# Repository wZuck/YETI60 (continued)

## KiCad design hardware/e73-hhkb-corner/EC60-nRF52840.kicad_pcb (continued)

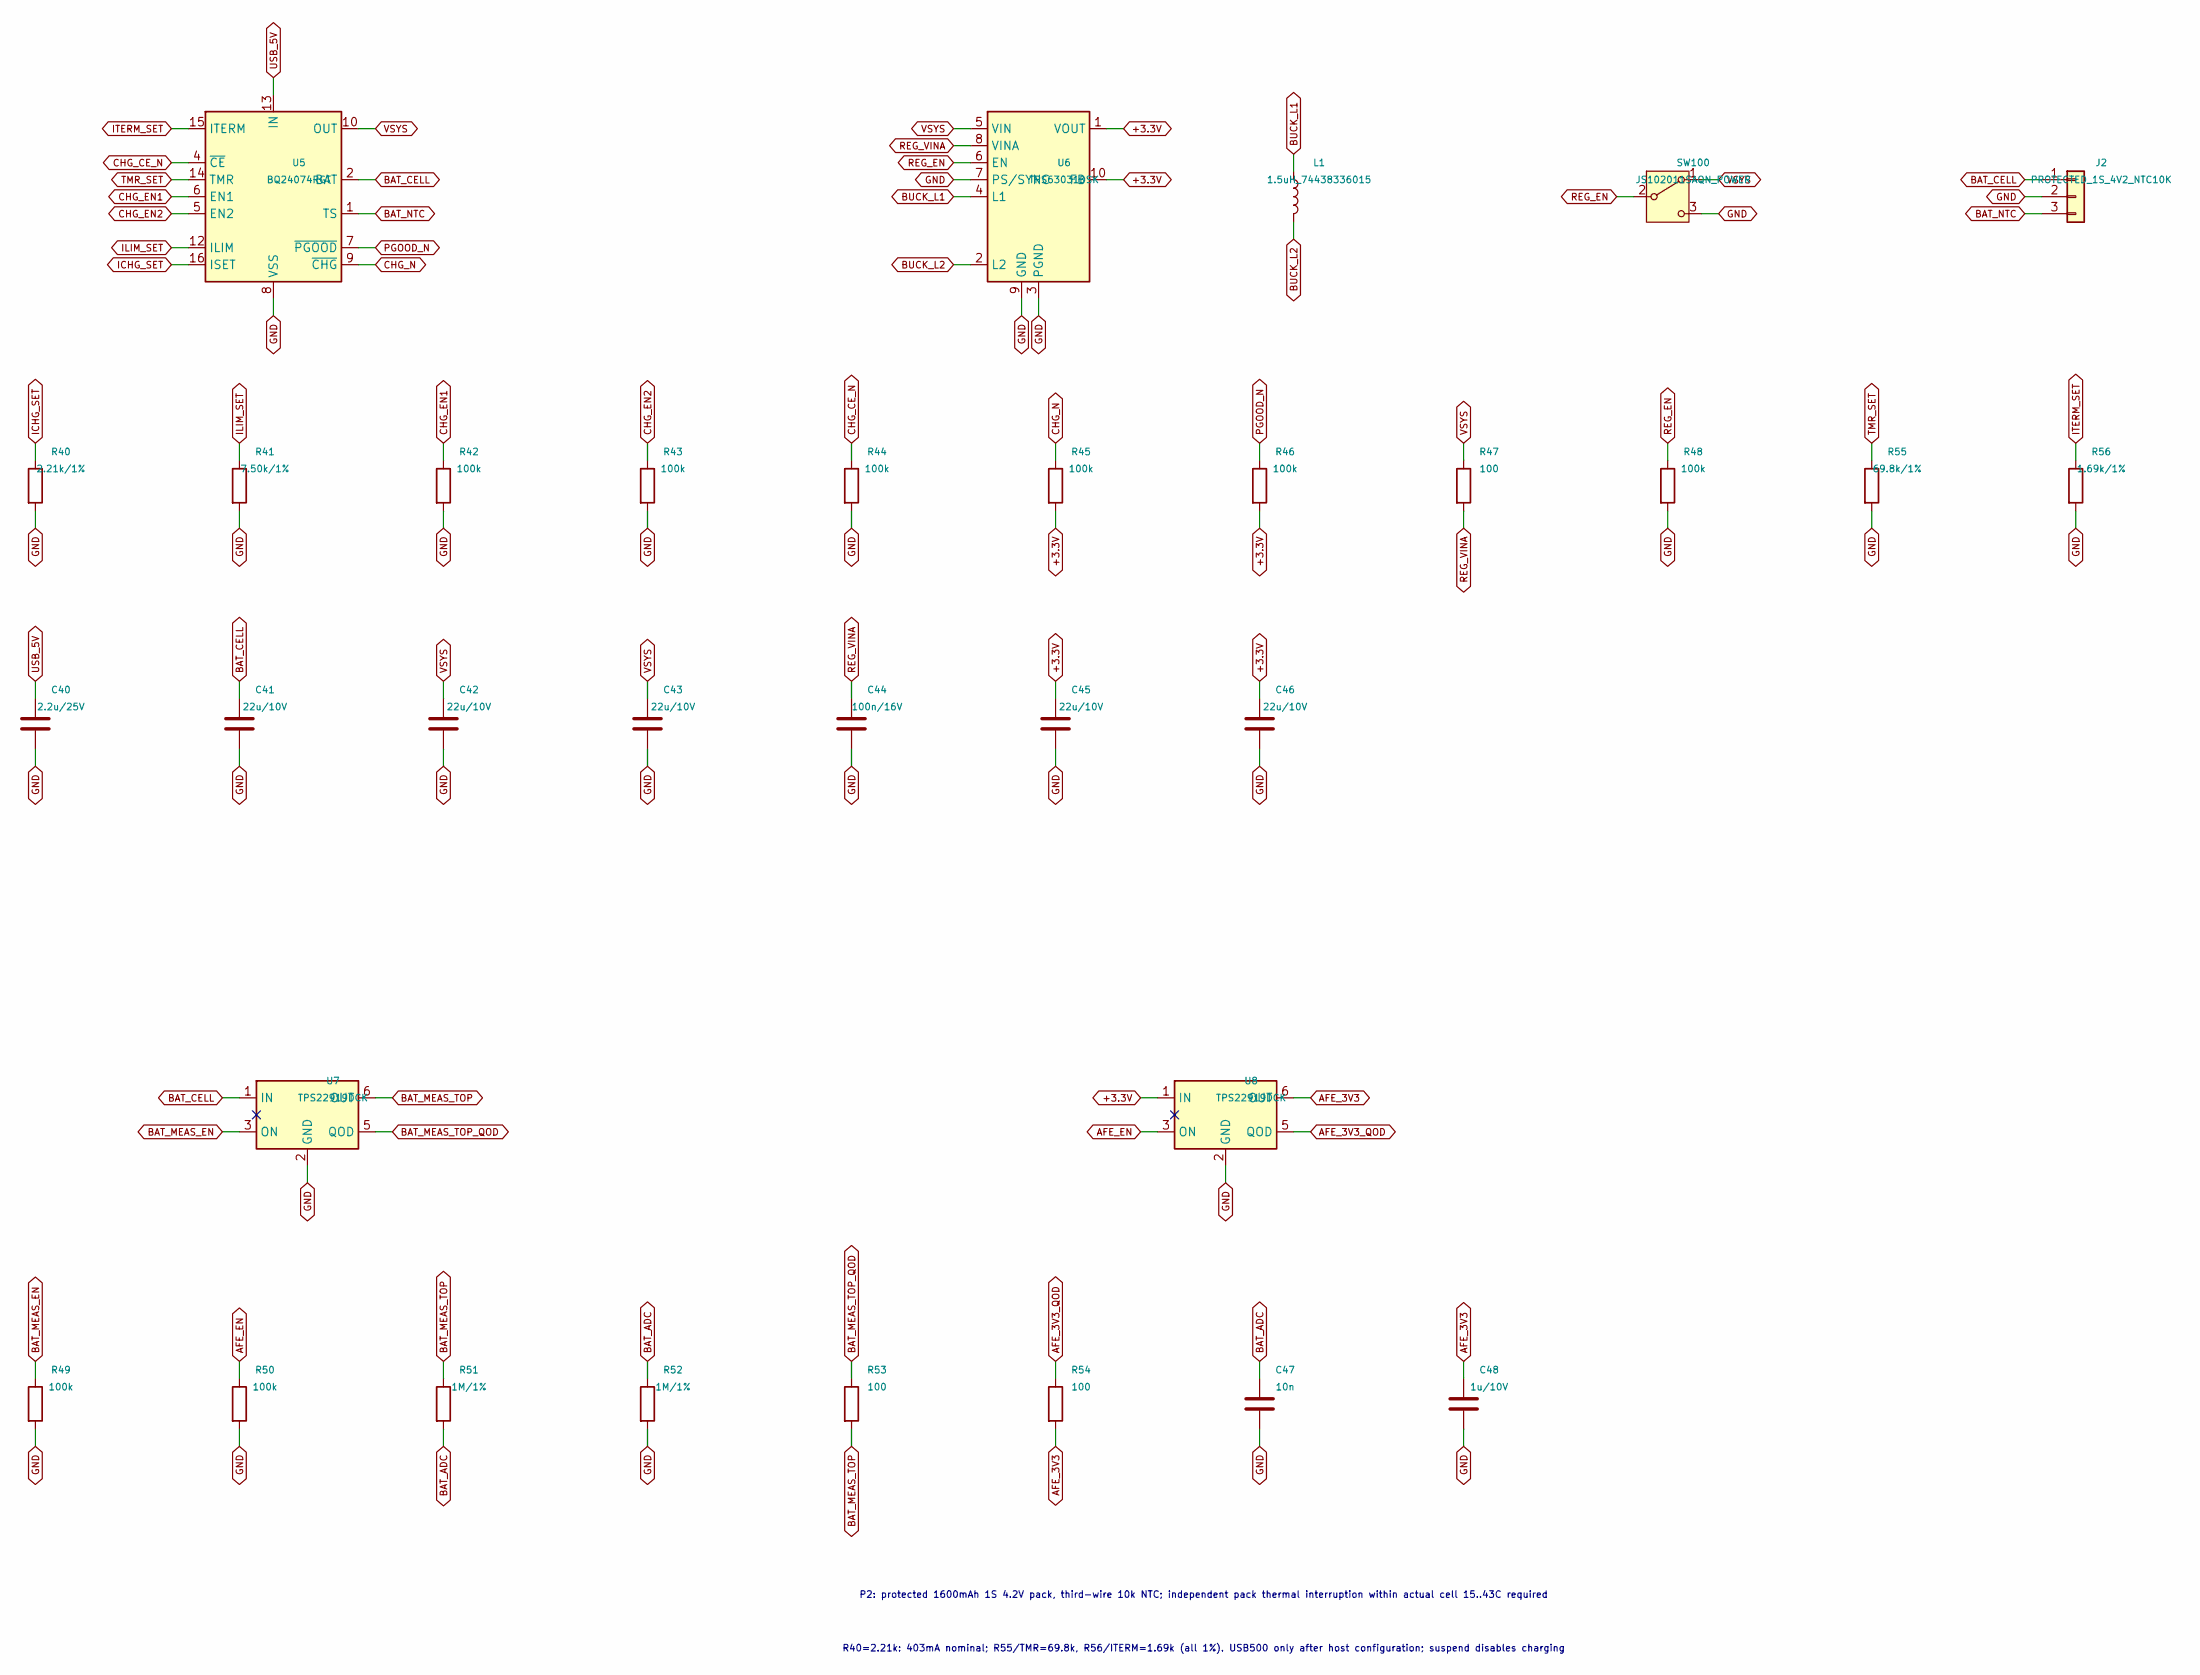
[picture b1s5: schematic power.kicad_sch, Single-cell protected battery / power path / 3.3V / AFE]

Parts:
C40: 2.2u/25V; C_0805_2012Metric__C40
C41: 22u/10V; C_0805_2012Metric__C41
C42: 22u/10V; C_0805_2012Metric__C42
C43: 22u/10V; C_0805_2012Metric__C43
C44: 100n/16V; C_0603_1608Metric__C44
C45: 22u/10V; C_0805_2012Metric__C45
C46: 22u/10V; C_0805_2012Metric__C46
C47: 10n; C_0402_1005Metric__C47
C48: 1u/10V; C_0402_1005Metric__C48
J2: PROTECTED_1S_4V2_NTC10K; JST_SH_SM03B-SRSS-TB_1x03-1MP_P1.00mm_Horizontal__J2
L1: 1.5uH_74438336015; L_Wuerth_MAPI-3015__L1
R40: 2.21k/1%; R_0402_1005Metric__R40
R41: 7.50k/1%; R_0402_1005Metric__R41
R42: 100k; R_0402_1005Metric__R42
R43: 100k; R_0402_1005Metric__R43
R44: 100k; R_0402_1005Metric__R44
R45: 100k; R_0402_1005Metric__R45
R46: 100k; R_0402_1005Metric__R46
R47: 100; R_0402_1005Metric__R47
R48: 100k; R_0402_1005Metric__R48
R49: 100k; R_0402_1005Metric__R49
R50: 100k; R_0402_1005Metric__R50
R51: 1M/1%; R_0402_1005Metric__R51
R52: 1M/1%; R_0402_1005Metric__R52
R53: 100; R_0402_1005Metric__R53
R54: 100; R_0402_1005Metric__R54
R55: 69.8k/1%; R_0402_1005Metric__R55
R56: 1.69k/1%; R_0402_1005Metric__R56
SW100: JS102011SAQN_POWER; SW_SPDT_CK_JS102011SAQN__SW100
U5: BQ24074RGT; VQFN-16-1EP_3x3mm_P0.5mm_EP1.6x1.6mm__U5
U6: TPS63031DSK; WSON-10-1EP_2.5x2.5mm_P0.5mm_EP1.2x2mm__U6
U7: TPS22919DCK; SOT-363_SC-70-6__U7
U8: TPS22919DCK; SOT-363_SC-70-6__U8

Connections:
+3.3V: C45.1, C46.1, R45.2, R46.2, U6.1 (VOUT), U6.10 (FB), U8.1 (IN); also elsewhere on the board
AFE_3V3_QOD: R54.1, U8.5 (QOD)
AFE_EN: R50.1, U8.3 (ON); also elsewhere on the board
BAT_ADC: C47.1, R51.2, R52.1; also elsewhere on the board
BAT_CELL: C41.1, J2.1, U5.2 (BAT), U5.3 (BAT), U7.1 (IN)
BAT_MEAS_EN: R49.1, U7.3 (ON); also elsewhere on the board
BAT_MEAS_TOP: R51.1, R53.2, U7.6 (OUT)
BAT_MEAS_TOP_QOD: R53.1, U7.5 (QOD)
BAT_NTC: J2.3, U5.1 (TS)
BUCK_L1: L1.1, U6.4 (L1)
BUCK_L2: L1.2, U6.2 (L2)
CHG_CE_N: R44.1, U5.4 (~CE); also elsewhere on the board
CHG_EN1: R42.1, U5.6 (EN1); also elsewhere on the board
CHG_EN2: R43.1, U5.5 (EN2); also elsewhere on the board
CHG_N: R45.1, U5.9 (~CHG); also elsewhere on the board
GND: C40.2, C41.2, C42.2, C43.2, C44.2, C45.2, C46.2, C47.2, C48.2, J2.2, R40.2, R41.2, R42.2, R43.2, R44.2, R48.2, R49.2, R50.2, R52.2, R55.2, R56.2, SW100.3 (C), U5.8 (VSS), U5.17 (VSS), U6.3 (PGND), U6.7 (PS/SYNC), U6.9 (GND), U6.11 (PGND), U7.2 (GND), U8.2 (GND); also elsewhere on the board
ICHG_SET: R40.1, U5.16 (ISET)
ILIM_SET: R41.1, U5.12 (ILIM)
ITERM_SET: R56.1, U5.15 (ITERM)
PGOOD_N: R46.1, U5.7 (~PGOOD); also elsewhere on the board
REG_EN: R48.1, SW100.2 (B), U6.6 (EN)
REG_VINA: C44.1, R47.2, U6.8 (VINA)
TMR_SET: R55.1, U5.14 (TMR)
USB_5V: C40.1, U5.13 (IN); also elsewhere on the board
VSYS: C42.1, C43.1, R47.1, SW100.1 (A), U5.10 (OUT), U5.11 (OUT), U6.5 (VIN)

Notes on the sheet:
P2: protected 1600mAh 1S 4.2V pack, third-wire 10k NTC; independent pack thermal interruption within actual cell 15..43C required
R40=2.21k: 403mA nominal; R55/TMR=69.8k, R56/ITERM=1.69k (all 1%). USB500 only after host configuration; suspend disables charging

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
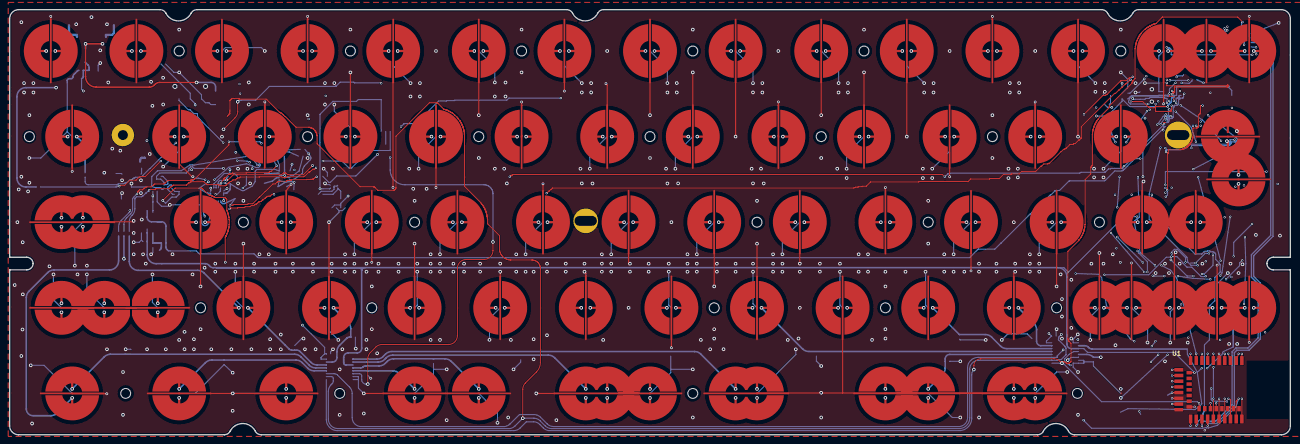
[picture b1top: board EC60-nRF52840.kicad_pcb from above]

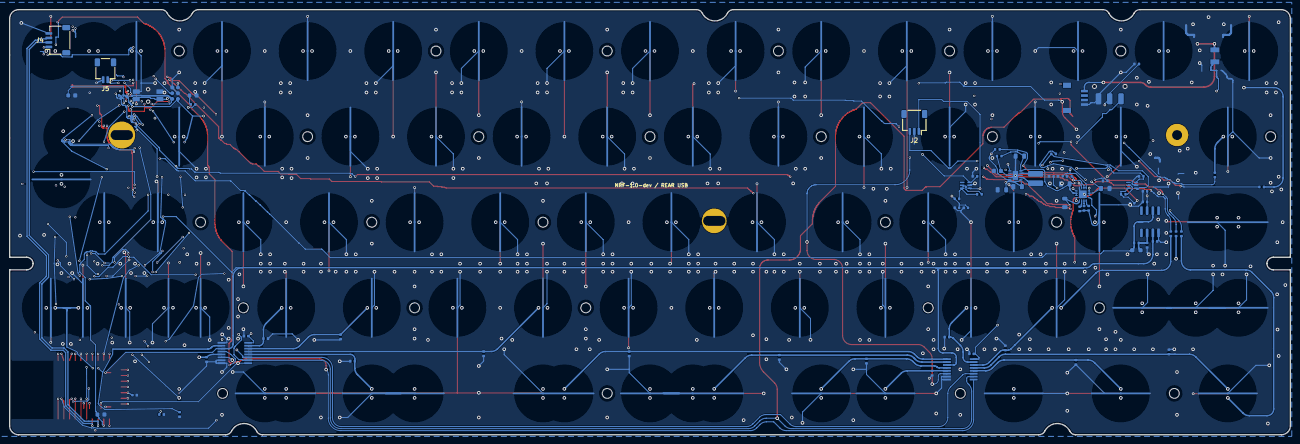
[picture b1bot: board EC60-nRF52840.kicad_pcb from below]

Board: 4 copper layers, 285.0 x 94.6 mm, 175 parts (76 on the bottom side), 68 nets.

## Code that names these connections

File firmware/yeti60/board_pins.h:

/* Generated by scripts/generate_yeti60_pin_contract.py; GPIO = port*32+pin. */
#pragma once
#include <stdint.h>
#define YETI_ROWS 5
#define YETI_COLS 15
#define YETI_ADC_AIN 4
#define YETI_BAT_AIN 3
#define PIN_ROW_DRV0 13
#define PIN_ROW_DRV1 43
#define PIN_ROW_DRV2 24
#define PIN_ROW_DRV3 41
#define PIN_ROW_DRV4 0
#define PIN_AMUX_SEL_0 20
#define PIN_AMUX_SEL_1 22
#define PIN_AMUX_SEL_2 15
#define PIN_APLEX_EN_PIN_0 1
#define PIN_APLEX_EN_PIN_1 9
#define PIN_APLEX_OUT_PIN_0 26
#define PIN_ADC 28
#define PIN_BAT_ADC 5
#define PIN_BAT_MEAS_EN 29
#define PIN_AFE_EN 31
#define PIN_CHG_EN1 3
#define PIN_CHG_EN2 2
#define PIN_CHG_CE_N 45
static const uint8_t yeti_rows[] = {13, 43, 24, 41, 0};
static const uint8_t yeti_sel[] = {20, 22, 15};
static const uint8_t yeti_en[] = {1, 9};
static const uint8_t yeti_channels[] = {0, 3, 1, 2, 5, 7, 6, 4, 0, 3, 1, 2, 5, 7, 6};
